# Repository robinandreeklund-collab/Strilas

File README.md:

# STRILAS

**Ballistic Laser Tactical-Engagement Simulator** — an open, DIY force-on-force training/gaming system. Players carry replica weapons that fire **coded infrared light** (not projectiles). Hits are registered by body/helmet detectors, ballistics and time-of-flight are simulated centrally, and every shot, movement, reload and hit is logged for live tracking and after-action review.

Think MILES / laser-tag, but with simulated ballistics, physical recoil feedback, NFC-based ammunition logistics, and an open telemetry stack you own.

> 📖 **Komplett systemguide (master-referens):** [`STRILAS-SYSTEM-GUIDE.md`](STRILAS-SYSTEM-GUIDE.md)
> — allt på ett ställe: arkitektur, ballistik/räckvidd, precision, hitbox, algoritm, optik, RTK-position,
> haptik, korten, batteritid, eye-safety, tillverkning, verifiering och repo-karta.
> Tillverkningsberedskap: [`vapen-stack/nextpcb/FORSTA-BATCH.md`](vapen-stack/nextpcb/FORSTA-BATCH.md).

---

## ⚠️ Safety first — read this before building anything

STRILAS is a **simulation and immersion** system. It does **not** fire projectiles and provides **no** uplift toward any real weapon. It does, however, contain three genuine hazards that you are responsible for handling correctly:

1. **Eye safety (IR laser).** The engagement emitter uses near-IR (~905 nm) which is **invisible**. Keep the optical output within **Class 1 (eye-safe)** limits and enforce the current limit **in hardware**, not just firmware. The risk is highest near the muzzle where players point at each other. If you are not confident you can keep it Class 1, use a diverged IR-LED emitter instead of a collimated laser diode.
2. **LiPo charging.** The base dock charges many lithium packs at once. This is the single largest fire risk in the project — larger than the laser. Use per-cell balancing, a real BMS, thermal monitoring, and a fire-safe charging area.
3. **High-current contacts.** The recoil rail carries ~20 A peaks through the magazine interface. Use contacts rated **> 25 A** and only ever make/break them **cold** (rail disabled during insert/extract — see the make-ready state machine).

**Replica / airsoft chassis:** STRILAS is typically built onto an airsoft replica body. Airsoft replicas are age- and region-restricted; check and follow your local laws for ownership, transport (e.g. muzzle covers / cases), and where you may use them. Treat and store the device responsibly and never carry it in public in a way that could be mistaken for a real firearm.

**Play safety:** eye protection (rated goggles) for all participants, defined play boundaries, and a clear "weapons safe" procedure.

---

## What it does

- **Coded IR engagement** — every shot transmits a packet (shooter ID, weapon profile, ammo/damage code). Detectors on harness + 360° helmet register hits and hit zones.
- **Simulated ballistics** — per-weapon/ammo profiles define muzzle velocity, drag model, drop and time-of-flight. Because the laser arrives instantly, the **server** adjudicates whether the simulated round would land, using both players' positions, the weapon's attitude and the computed flight time.
- **Physical recoil** — an electronic reciprocating-mass unit gives a real kick, scaled per weapon profile. The IMU senses the muzzle climb it causes and feeds it into the **next** shot's trajectory (the recoil-to-aim loop), so uncontrolled bursts walk off target.
- **NFC ammunition logistics** — each magazine carries a passive NFC tag (ID, capacity, rounds remaining). Inserting a mag sets the ammo counter; running dry blocks fire; reloading rewrites the tag to full at base.
- **Make-ready drill** — the recoil power rail (sourced from a battery inside the magazine) is enabled only after racking a charging handle, mirroring "chamber a round," and disabled before the magazine is released. This also guarantees the high-current contacts are always made/broken cold.
- **Live positioning & telemetry** — UWB (+ GNSS outdoors) gives sub-30 cm position; body/weapon IMUs give pose. Everything is timestamped to a shared clock.
- **After-action review** — weapon-cam video synced with the full event timeline, plus a live dashboard and map.

---

## How it works (engagement model)

```
trigger ──► IR emitter sends coded pulse ──► target detector registers strike
   │                                                  │
   └─► recoil unit fires (PWM scaled)                 │
   └─► IMU captures barrel attitude                   ▼
                                       SERVER adjudicates:
                                       shooter pos + target pos (UWB/GNSS)
                                       + barrel attitude (IMU)
                                       + simulated time-of-flight & drop
                                       ──► hit / miss / hit-zone outcome
```

The key design choice is **central, positional adjudication**: rather than computing the result on each weapon, the server knows where both parties are and how they are moving, and resolves the engagement with the simulated projectile's flight time. This is fairer for moving targets and is the basis for the analytics layer.

---

## Project map (design → validated → runnable)

This repo has grown from the spec above into a **physically-validated design with a runnable
reference implementation**. Where to look:

| Area | What | Where |
|---|---|---|
| **Analysis & BOM** | README review + state-of-the-art level-3 BOM + chosen dev boards | [`docs/hardware-analysis.md`](docs/hardware-analysis.md) |
| **Architecture** | geometric ballistic adjudication + fused pose stack (incl. precision ≠ beam width) | [`docs/level3-ballistic-architecture.md`](docs/level3-ballistic-architecture.md) |
| **System flow** | how it all connects (component map, shot sequence, pose layers) | [`docs/system-flowchart.md`](docs/system-flowchart.md) |
| **v1 build** | exact shopping list for a precise 100–150 m shooting test | [`docs/mvp-shooting-test-bom.md`](docs/mvp-shooting-test-bom.md) |
| **Weapon PCB** | optic module: camera + 2× 940 nm emitters + IMU + buck-CC driver (42×62 mm) | [`hardware/README.md`](hardware/README.md) |
| **Receiver PCBs** | vest detector patch + helmet halo (TSOP + 860 nm constellation + GNSS) | [`hardware/receiver-boards.md`](hardware/receiver-boards.md) |
| **Design resolution** | every open problem → decision (wavelength split, eye safety, etc.) | [`hardware/weapon-module-design-resolution.md`](hardware/weapon-module-design-resolution.md) |
| **Eye safety** | Class 1 current budget (script + report) | [`hardware/eye-safety-budget.md`](hardware/eye-safety-budget.md) |
| **Physics verification** | end-to-end @150 m (radiometry + Monte Carlo + link budget) | [`hardware/system-verification-report.md`](hardware/system-verification-report.md) |
| **Firmware/CV** | runnable, hardware-abstracted chain (CV → fire-control → server) — no HW needed | [`firmware/README.md`](firmware/README.md) |
| **3D simulator** | interactive level-3 pipeline in the browser | [`sim/README.md`](sim/README.md) |

Run it (no hardware): `python3 -m firmware.run_demo` · `python3 -m firmware.test_chain` ·
`python3 hardware/system_physics_verification.py`

The key design choice — **central, positional adjudication** — is fully realized in
[`firmware/adjudicator.py`](firmware/adjudicator.py): the server knows where both parties are and
how they move, and resolves the engagement with the simulated projectile's flight time.

---

## System architecture

```
PLAYER NODE ×N
  ├─ Weapon unit (ESP32 + IMU)   ── ballistics, recoil control, state machine, radio
  ├─ IR emitter (905 nm, coded)
  ├─ Recoil unit (reciprocating mass)   ◄── powered by magazine LiPo via load-switch
  ├─ Harness + 360° helmet detectors
  ├─ Magazine (NFC tag + recoil LiPo + power contacts)
  ├─ Charging-handle & mag-release sensors  (make-ready / cold-mate sequencing)
  ├─ Internal logic cell  ── keeps node alive without a magazine
  └─ Weapon camera
        │  ESP-NOW / WiFi
        ▼
NETWORK (field)
  ├─ UWB anchors ×4–8   (sub-30 cm trilateration)
  ├─ WiFi mesh AP        (telemetry + video backhaul)
  └─ [optional] LoRa gateway + GNSS beacons   (large outdoor fields, coarse/long-range)
        │
        ▼
SERVER / EXERCISE CONTROL
  ├─ Hit adjudicator      (position + attitude + flight time → outcome)
  ├─ Position engine      (UWB + GNSS + IMU fusion → live map)
  ├─ Telemetry DB         (shots · movement · recoil · hits · ammo · make-ready)
  └─ AAR / replay + live dashboard
```

---

## Hardware (reference BOM, per player)

| Subsystem | Part (reference) | Notes |
|---|---|---|
| Weapon MCU | ESP32 (WiFi/BLE/ESP-NOW) | the brain; timing-critical IO |
| IMU | BNO085 (or BNO055) | barrel attitude + muzzle climb |
| IR emitter | 905 nm pulsed module + constant-current driver | **Class 1**, hardware current limit |
| Detectors | IR receiver array (harness) + 360° helmet sensor | hit + hit-zone |
| NFC reader | PN532 (I²C/SPI) + magwell switch | wakes on mag insert |
| Magazine tag | NTAG215 (passive) | ID / capacity / remaining |
| Recoil unit | reciprocating-mass actuator | ~0.12 kg moving mass, ~30 mm stroke |
| Recoil switching | logic-level MOSFET load-switch (>30 A) + flyback diode + 2×2200 µF low-ESR | soft-start |
| Magazine battery | high-discharge LiPo (≥25C) | powers recoil rail only |
| Logic battery | small internal 1S/2S cell + buck | keeps node alive without mag |
| Tracking | UWB tag (e.g. DW3000) + GNSS + body IMU | sub-30 cm + pose |
| Camera | ESP32-CAM / RunCam (5.8 GHz FPV or WiFi) | AAR + live |
| HUD | micro-OLED (SPI) | ammo · hits · weapon state |
| Sensors | charging-handle + mag-release micro-switches/hall | make-ready sequencing |

**Infrastructure:** UWB anchors ×4–8, WiFi mesh AP, server host, multi-bay LiPo charging dock (with BMS), optional Heltec CubeCell (HTCC-AB02S) boards as GNSS beacons / LoRa gateway for large outdoor fields.

> The CubeCell boards are **not** suitable as the weapon MCU (no WiFi/BLE, low-power M0+ core, LoRa is low-rate/duty-cycle-limited). Use them only for coarse outdoor GNSS beaconing or as a long-range LoRa gateway.

---

## Power architecture

Two physical sources, deliberately separated:

- **Logic rail** — internal cell → buck (3V3/5V) → MCU, IMU, IR driver, NFC, camera, OLED, radio. ~0.95 A average.
- **Recoil rail** — magazine LiPo → cold-mate power contacts → MOSFET load-switch (soft-start) → cap bank → recoil motor. ~4 A average, ~20 A peaks during full-auto.

The recoil rail is enabled by the MCU **only between "rack" and "mag release"**, so the magazine contacts are never made or broken under load.

---

## Make-ready state machine

```
NO MAG ──insert mag──► MAG IN (rail OFF, cold contacts)
                          │
                          └─ rack charging handle ─► validate (mag present, ammo>0)
                                                     ─► soft-start recoil rail
                                                     ─► chamber ─► READY (rail ON)
READY ──trigger──► IR + recoil, ammo−1 ──► READY
READY ──ammo == 0──► EMPTY (fire blocked, bolt-lock)
EMPTY ──swap mag + re-rack──► READY
ANY  ──mag-release──► drop rail FIRST ─► mag out (cold) ─► NO MAG
```

---

## Magazine NFC tag layout

| Field | Size | Contents |
|---|---|---|
| UID | 7 B | fixed magazine ID (read-only) |
| Capacity | 2 B | max rounds |
| Remaining | 2 B | current rounds |
| Profile | 1 B | weapon/ammo type |
| HMAC (optional) | 4–8 B | signature to prevent tampering |

Notes:
- The live count is held in **weapon RAM** while seated; the tag is written **once on extraction** (and once on base reload), staying well within EEPROM endurance.
- **Ammo count and battery charge are separate quantities.** Base reload is two decoupled cycles: a fast NFC ammo rewrite, and a slow BMS-managed battery charge. Keep a pool of magazines in rotation.
- For competitive integrity, sign `remaining` with an HMAC shared by weapon and base; mirror counts server-side per mag ID as backup.

---

## Weapon profile (example)

```yaml
# profiles/m4_556.yaml
name: "M4 / 5.56 sim"
muzzle_velocity_mps: 880
drag_model: G7
ballistic_coefficient: 0.151
rof_rpm: 720           # capped by recoil cycle time (~12 Hz)
recoil_pwm: 0.65       # 0..1 felt-recoil scale
mag_capacity: 30
damage_code: 0x12
```

---

## Repository structure

```
strilas/
├─ firmware/
│  ├─ weapon-node/        # ESP32: ballistics, recoil FSM, IR, NFC, IMU, radio
│  ├─ tracking-tag/       # UWB + GNSS + IMU beacon
│  ├─ base-dock/          # NFC rewrite + charge sequencing + logging
│  └─ detectors/          # harness / helmet receiver
├─ server/
│  ├─ adjudicator/        # positional hit resolution + flight-time model
│  ├─ position-engine/    # UWB/GNSS/IMU fusion
│  ├─ telemetry-db/       # time-series store
│  └─ dashboard/          # live map + AAR replay
├─ hardware/
│  ├─ weapon-unit/        # schematics, PCB, enclosures
│  ├─ magazine/           # tag + LiPo + contacts
│  └─ base-dock/          # multi-bay charger + BMS
├─ profiles/              # weapon/ammo YAML
├─ docs/
│  └─ strilas-systemritning.html   # full schematic set
└─ README.md
```

---

## Build & flash (outline)

> Detailed per-module instructions live in each subfolder's README.

```bash
# Weapon node (ESP32, PlatformIO)
cd firmware/weapon-node
pio run -t upload

# Server (dev)
cd server
docker compose up        # adjudicator + position-engine + telemetry-db + dashboard
```

Configuration (network keys, UWB anchor coordinates, weapon profiles) is set in `config/` — see `config/example.env`.

---

## Calibration & pre-game checklist

- [ ] IR emitter verified within Class 1 limits (hardware current limit confirmed).
- [ ] IR/detector boresight and range check; hit-cone divergence set per play style.
- [ ] UWB anchors surveyed; position fix < 30 cm in the play area.
- [ ] Recoil rail soft-start verified; no contact arcing on rack/mag-release.
- [ ] Magazine tags initialised (ID, capacity, profile); base reload writes full.
- [ ] All LiPos balanced/charged on the BMS dock; no swollen cells.
- [ ] Clocks synced across nodes (NTP/PTP); telemetry logging confirmed.
- [ ] Eye protection issued; boundaries and "weapons safe" briefed.

---

## Roadmap

- [ ] Environmental ballistics (wind, temperature) in the flight model.
- [ ] AR reticle/HUD overlay in the optic.
- [ ] Auto-generated engagement clips in AAR (tag video by event).
- [ ] Optional LoRa layer for large outdoor fields.
- [ ] Bolt-lock-back + muzzle-report audio for empty/feedback realism.

---

## Contributing

Issues and PRs welcome. Please keep the safety constraints (IR class, cold-mate contacts, BMS charging) non-negotiable in any hardware change, and document power/timing implications for changes that touch the recoil or engagement path.

---

## License

- Code: MIT
- Hardware: CERN-OHL-S
- Docs: CC BY 4.0

*(Adjust to taste before publishing.)*

---

*STRILAS is a training/gaming simulator. It is not a weapon and provides no real-world weapon capability. Build and operate it responsibly and within your local laws.*

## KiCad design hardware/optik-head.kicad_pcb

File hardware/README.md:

# STRILAS — Hårdvaruritningar

Två fysiskt skilda noder, två kort:

| Kort | Nod | Funktion | Doc |
|---|---|---|---|
| **Vapnets optikmodul** | vapen | precis sikteskamera + IR-**sändare** (940 nm) + IMU + driver | nedan |
| **Väst-detektor-patch** | väst | IR-**mottagare** (TSOP 940 nm) + 860 nm-konstellation | [receiver-boards.md](receiver-boards.md) |
| **Hjälm-halo** | hjälm | 8× TSOP 360° + 860 nm-konstellation + **GNSS-patch** | [receiver-boards.md](receiver-boards.md) |

*(Föråldrad: `detector-ring-8x-tsop4856` hade kamera i mitten — player har ingen kamera; ersatt av väst-patch + hjälm-halo.)*

---

## 1. Vapnets optikmodul v1 (KOMPAKT) — sikteskamera + 2× IR-emitter + IMU + driver

**Allt vapnet behöver** på ett kort: precist sikte, skottstråle, attityd och driver.
Krympt från Ø80 (4 emittrar) till **42×62 mm** *utan prestandaförlust*. Genereras av
[`weapon_emitter_layout.py`](weapon_emitter_layout.py).

> **Full designupplösning (alla problem → beslut):** se
> [`weapon-module-design-resolution.md`](weapon-module-design-resolution.md).

**Precisionen** kommer från **sikteskameran** (centrum) som mäter bäringen till målets
IR-konstellation → sub-0,1° (se `../docs/level3-ballistic-architecture.md` §3.2) — den är
**oförändrad oavsett emitterantal**. **Skottet** är de 2 kollimerade emittrarna, symmetriskt
ovanför kameran → **samboresikt** (parallax ~0,01° @150 m; bred kon = bara LOS/ID).

### Vad som sitter på kortet

| Ref | Del | Roll |
|---|---|---|
| (mitten) | **Sikteskamera: OV5647 NoIR + 860 nm bandpass + M12 (FOV 15–30°)** | **PRECISION** — ser konstellationen → solvePnP → bäring (rolling shutter; fast-pan-grind i firmware) |
| D1–D2 | **940 nm OSLON Black** ×2 + **Carclo 10195** (~Ø20) kollimator | **skott** — kodad 56 kHz-stråle, 100–150 m |
| U2 | **TDK ICM-45686 IMU (SPI)** | attityd mellan kamerabildrutor + rekyl; **array borttagen — verifierat 1 räcker** (drift 0,0005°) |
| U6 / L1 / Rsense | **buck konstantströms-LED-driver** (från 2S) / induktor / sense-resistor | konstantström + **hårt HW-tak = ögonsäkerhet** |
| C1 / Cin / D5 / Q1 | Cout 220 µF / in-cap / freewheel-diod / AO3400 **56 kHz-gate** | switch-passiva + bärvågs-gate |
| Q2 / TVS / F1 | reverse-FET / clamp / PTC | inskydd på VBAT |
| J1 | **2×5 SPI:** VBAT·EN·IR_MOD·SCK·MOSI / GND·3V3·GND·MISO·CS | mot ESP32-P4 (kamera via FFC) |

### Mått & el — och varför prestandan hålls

- Kort **42 × 62 mm** (rundad rektangel), 3× M2.5. **~48 % mindre yta än Ø80**, halva bredden.
- **2 LED i serie** delar effektlasten → 100–150 m bibehålls; **VBAT 2S in**, U6 **buck-CC** steg ner (boost ej nödvändig); **IR_MOD** = 56 kHz på Q1-gaten.
- **1 IMU på SPI** (SPI för hög ODR vid rekyl). Array **borttagen** — fysik-verifieringen visade inter-frame-drift 0,0005° ≪ krav.
- **Precision = kameran** (emitter- & IMU-antal påverkar inte rubrik-precisionen — kameran 90 fps GS är primär referens).

### ✅ Självbländning — LÖST via våglängdssplit

**SKOTT = 940 nm**, **kamera = 860 nm bandpass** → kameran **avvisar sina egna emittrar**.
Inget timing-/baffelberoende (baffel kvar som backup). Bonus: 940 nm = TSOP-topp, 860 nm =
bättre kisel-QE för konstellationen. (Detaljer: design-resolution §0.)

### ⚠️ Ögonsäkerhet (mätpunkt)

Buck-CC-drivern (U6) ger **hårt HW-strömtak** (sense-resistor; firmware bara lägre).
**150 m kräver ~2 A** med medium-lins (10195) → Eavg ≈ 18× *punktkälle*-MPE @100 mm; **extended-
source-relaxationen täcker** men **måste mätas** (AE/skenbar källa per IEC 60825-1).
**Bringup: börja 1 A.** Notera: **ögonexponeringen sätts av 150 m-räckviddskravet (~Ie 59 W/sr),
ej av linsvalet** — medium @ 2 A ≈ minsta möjliga exponering. (Verifiering + design-resolution §3.)

### ⚠️ Kamera = OV5647 (kit), men MÅSTE vara NoIR

Kit-kameran är **Raspberry Pi Camera Model B = OV5647** (5 MP, 1/4″, M12 6 mm/F2.0/60,6° diag),
P4-stödd. **MEN spec säger "IR night vision: nonsupport" → den har IR-cut-filter och ser INTE
860 nm.** Vår precisionsväg kräver att kameran ser målets 860 nm-konstellation, så:
**du måste använda NoIR-varianten** (ta bort IR-cut-filtret, eller köp RPi NoIR-kameran).
Utan det ser sikteskameran ingen konstellation.

- **Stock-lins 6 mm/F2 (~33° H):** fungerar (verifierat SNR ≈ 30 @150 m, kort exp) men mindre
  marginal. **M12-linsen är utbytbar** → längre brännvidd ger mer räckvidd/SNR om du vill.
- Rolling shutter hanteras med kort exponering + modulerade LED + **fast-pan-grind** i firmware.

**GS-uppgradering om grinden blir för begränsande:** **ams-OSRAM MIRA220MINI MONO** (global shutter,
NIR) — köpbar (DigiKey **~$141**), men **eval-/sensorkort**, inte ett färdigt kit → P4-integration
gör du själv (ams-OSRAM-exempel finns); footprint ur deras öppna PCB-filer.

**Inte** IMX296/Arducam Pivariety (= Pi). Fullt kameraval: [`camera-selection.md`](camera-selection.md).

---

## 2. Detektor-ring (MÅLSIDAN) — 8× TSOP4856 + kamera

**Målets/västens** mottagarmodul (du skjuter MOT den) — 8 IR-mottagare i ring runt en
kamera. Genereras av [`detector_ring_layout.py`](detector_ring_layout.py). Separat nod
från vapnet; specen för mått/avkoppling/360°-täckning står i skriptets noter.

> Den här hör hemma på målet/västen, inte på vapnet — vapnet **sänder** (kort 1),
> målet **tar emot** (kort 2).

---

## Nästa steg mot riktig PCB

Dessa ritningar → KiCad: SFH 4715AS- + TSOP4856- + kameramodul-footprints, dragning till
header. Säg till så genererar jag KiCad-footprintsen och ett schema.

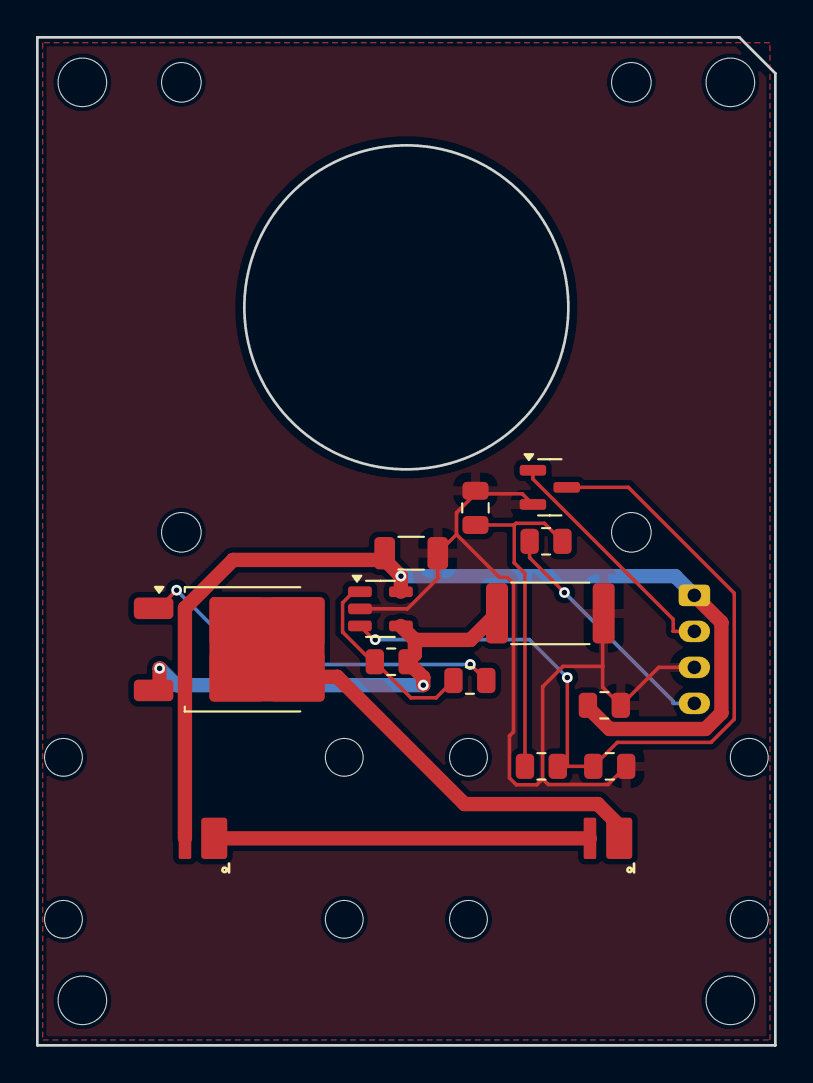
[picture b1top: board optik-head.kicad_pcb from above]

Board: 2 copper layers, 41.0 x 56.0 mm, 31 parts (1 on the bottom side), 11 nets.

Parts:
C1: 100nF; R_0805_2012Metric
C2: 100pF; R_0805_2012Metric
C3: 22uF; C_1206_3216Metric
C4: 1uF; C_0805_2012Metric
CAM1, CAM2, CAM3, CAM4: MountingHole_2.2mm_M2
CL1, CL2, CL3, CL4, CL5, CL6, CL7, CL8: MountingHole_2.1mm
D1, D2: SFH4725AS_940nm; IR_Emitter_OSRAM_OSLON_Black_SFH4725S
J1: →HAT (VBAT·IR_MOD·GND·EMIT_SET); JST_PH_B4B-PH-K_1x04_P2.00mm_Vertical
MH1, MH2, MH3, MH4: MountingHole_2.7mm_M2.5
Q1: AOD4184A; TO-252-2
Q3: AO3400; SOT-23
R1: 0R068; R_2512_6332Metric
R3: 15k; R_0805_2012Metric
R4: 1k; R_0805_2012Metric
R5: 100R; R_0805_2012Metric
R7: 10k; R_0805_2012Metric
U1: OPA171; SOT-23-5

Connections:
DRV_GATE: Q1.1, R5.2
EMIT_SET: J1.4, R7.1
GND: C1.2, C3.2, C4.2, J1.3, Q3.2, R1.2, R4.2, U1.2
IDRV_REF: Q3.3, R3.2, R4.1, U1.3
IDRV_SENSE: C2.2, Q1.3, R1.1, U1.4
IR_MOD: J1.2, Q3.1
LED_CATH: D2.2, Q1.2
LED_MID: D1.2, D2.1
OPA_OUT: C2.1, R5.1, U1.1
VBAT: C1.1, C3.1, D1.1, J1.1, U1.5
V_SET: C4.1, R3.1, R7.2

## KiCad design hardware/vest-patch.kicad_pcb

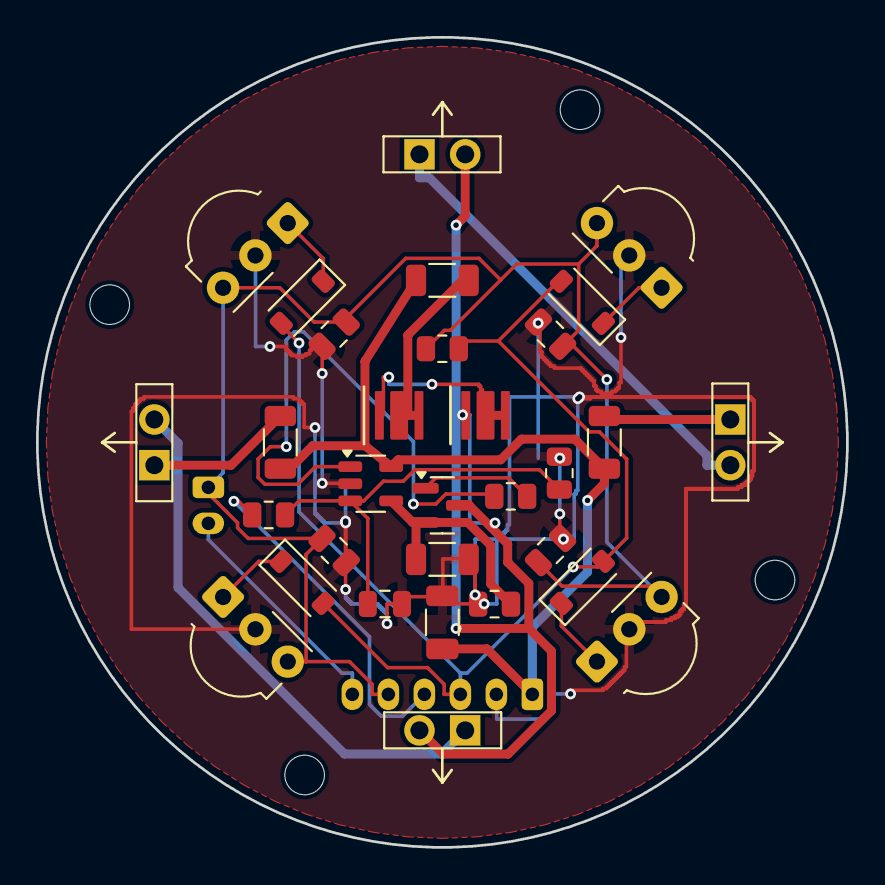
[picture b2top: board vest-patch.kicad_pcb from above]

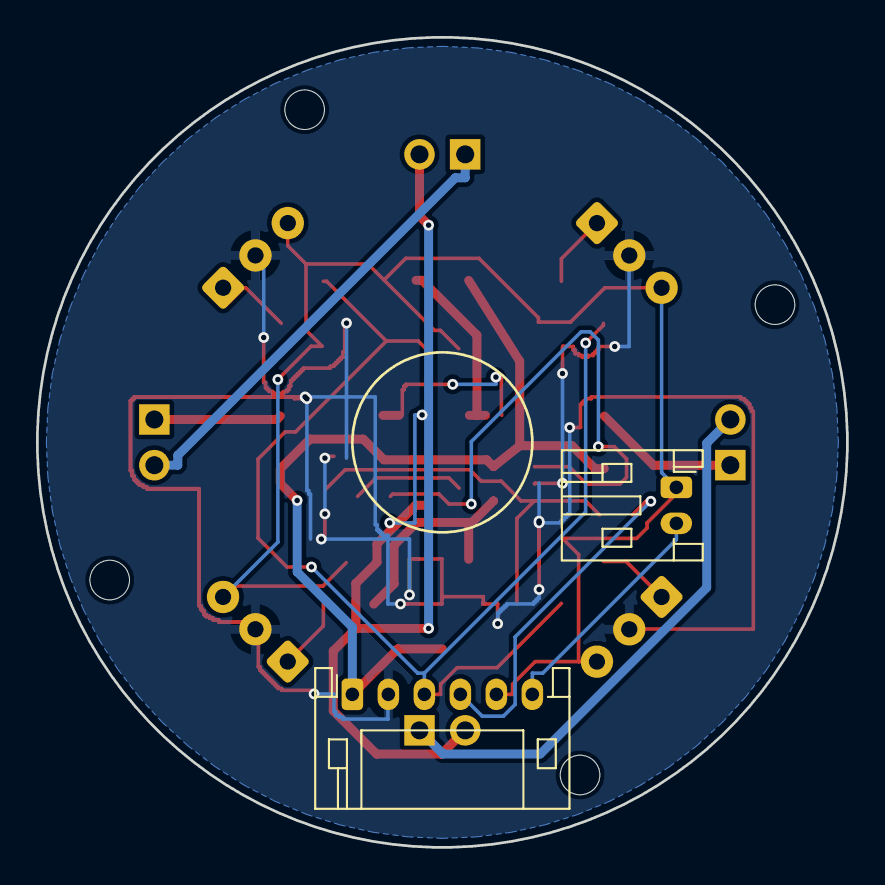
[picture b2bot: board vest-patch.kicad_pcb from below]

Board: 2 copper layers, 45.0 x 45.0 mm, 38 parts (3 on the bottom side), 21 nets.

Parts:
C1: C_1206_3216Metric
C2, C3, C4, C5: C_0805_2012Metric
C6: 22nF; C_0805_2012Metric
D1, D2, D3, D4: D_SOD-123
D5, D6: L1I0_IR
D7, D8, D9, D10: LED_Tab
H1, H2, H3, H4: MountingHole_2.2mm_M2
J1: JST_PH_S6B-PH-K_1x06_P2.00mm_Horizontal
J2: JST_PH_S2B-PH-K_1x02_P2.00mm_Horizontal
MK1: ERM_Coin_Keepout_10mm
Q1: SOT-23
R1, R2, R7, R8, R9: R_0805_2012Metric
R3, R4, R5, R6: R_1206_3216Metric
U1, U2, U3, U4: Vishay_MOLD-3Pin
U5: SOT-23-5

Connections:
+3V3: C2.1, C3.1, C4.1, C5.1, J1.5, J2.1, R1.1, U1.3, U2.3, U3.3, U4.3
DATA: D1.2, D2.2, D3.2, D4.2, J1.3, R1.2
GND: C1.2, C2.2, C3.2, C4.2, C5.2, C6.2, J1.2, R6.2, R7.1, R9.2, U1.2, U2.2, U3.2, U4.2, U5.2
IDRV_REF: C6.1, R8.2, R9.1, U5.3
IDRV_SENSE: Q1.2, R6.1, R7.2, U5.4
LED_A1: D5.1, R3.2
LED_A2: D7.1, R4.2
LED_A3: D9.1, R5.2
LED_CATH: D6.2, D8.2, D10.2, Q1.3
LED_EN: J1.4, R8.1
LED_GATE: Q1.1, R2.2
LED_M1: D5.2, D6.1
LED_M2: D7.2, D8.1
LED_M3: D9.2, D10.1
unnamed: R2.1, U5.1
OUT1: D1.1, U1.1
OUT2: D2.1, U2.1
OUT3: D3.1, U3.1
OUT4: D4.1, U4.1
VBAT: C1.1, J1.1, R3.1, R4.1, R5.1, U5.5
VIB: J1.6, J2.2

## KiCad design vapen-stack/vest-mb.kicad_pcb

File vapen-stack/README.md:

# STRILAS — vapen-stack (ren leveransmapp)

Allt för den kompletta vapen-stacken i **en mapp**: tre kort, hopsättnings-STEP,
verifiering och komplett BOM. Källkoden (generatorerna) ligger kvar i `../hardware/`.

## Stacken (uppifrån och ned)
```
FC-kort   (fire-control)  ── socket J1 → P4 edge A (12)  ·  J2 → P4 edge B (3V3-tapp)
ESP32-P4  (Waveshare)     ── edge A uppåt (FC) · edge B nedåt (optik)
Optik     (weapon-module) ── socket J1 → P4 edge B (14)  ·  lins Ø16 fram
```
Kraft: **batteri → optik J2 → VBAT → P4 VSYS → P4-regulator → 3V3 → alla kort**
(FC tar 3V3 direkt från edge B via J2 — ingen kabel/bygel).

## Filer

**Färdiga kort (beställ/tillverka):**
| Kort | PCB | 3D | Gerbers |
|---|---|---|---|
| Optik | `weapon-module.kicad_pcb` | `weapon-module.step` | `weapon-module-gerbers.zip` |
| P4-carrier* | `p4-board.kicad_pcb` | `p4-board.step` | — (köps, ej PCB) |
| Fire-control | `firecontrol.kicad_pcb` | `firecontrol.step` | `firecontrol-gerbers.zip` |

\* P4 = köpt **Waveshare ESP32-P4-WIFI6**. `p4-board.*` är mekanik-/headermodell.

**Hopsättning i Fusion (co-orienterade — droppa in vid origo, utan rotation):**
`weapon-module.step` (ankare) · `p4-board-stack.step` · `firecontrol-stack.step`
→ lyft P4 och FC i Z (~socket+header-höjd). USB-kabelpluggen i J_CAM kräver
clearance i P4↔optik-gapet.

**Färdig hop-assembly (allt i en fil):** `strilas-assembly.step` — alla tre korten
i en STEP, co-orienterade, **12 mm plan-till-plan** (optik z0 · P4 z12 · FC z24).
Standoffs läggs in av användaren. Regenereras med `python3 merge_assembly_step.py`
(kräver `pip install cadquery` — bygger en korrekt OCCT-assembly, stel Z-placering).

**BOM:** `BOM.csv` · `BOM.md` (komplett, alla kort + externa moduler). Regenereras
med `python3 gen_bom.py`.

**Verifiering:** `python3 system_sim.py` → ström-/signalflöde över kortgränserna
(0 typkrock · 0 utan ström · 0 dinglar). Bilder (regenereras ur live-netlista/-geometri):
- `port-matching.png` — varje stift etiketterat, mate-par med ✓ (`render_port_labels.py`)
- `edgeB-match-proof.png` — edge B↔optik: alla 14 stift + 4 hål, standoff-låst,
  speglad mate J1.k↔P4-stift(15-k), verifierad 0.000 mm (`render_edgeb_proof.py`)
- `system-flow.png` — kraft-/databuss-översikt

> **Mate (verifierat 0.000 mm mot _pads_z-geometrin):** P4 edge B är flippad till baksidan
> (J_B) → STACKAD/speglad mate, så optik **J1.k ↔ P4 edge B-stift (15-k)** (J1.1↔GPIO32 …
> J1.14↔VSYS). Edge A (FC) är på framsidan → RAK mate (FC J1.k ↔ edge A-stift k+5).
> De 5 IMU/SPI-näten ligger på J1-stift {1,2,4,6,7} = GPIO {32,27,26,23,22} och är
> permuterade för planär (korsningsfri, via-fri) routning IMU→J1 på F_Cu.

**Footprints:** `strilas.pretty/` (IR-emitter + ICM-456xx IMU).

**Design-noter:** `firecontrol.md` · `weapon-module-fab.md`

## Regenerera (källa i ../hardware/)
```
python3 hardware/weapon_module_netlist.py   &&  python3 hardware/receiver_place.py weapon
python3 hardware/make_p4_board.py
python3 hardware/firecontrol_netlist.py     &&  python3 hardware/receiver_place.py firecontrol
python3 hardware/export_stack_step.py        # co-orienterade STEP
```

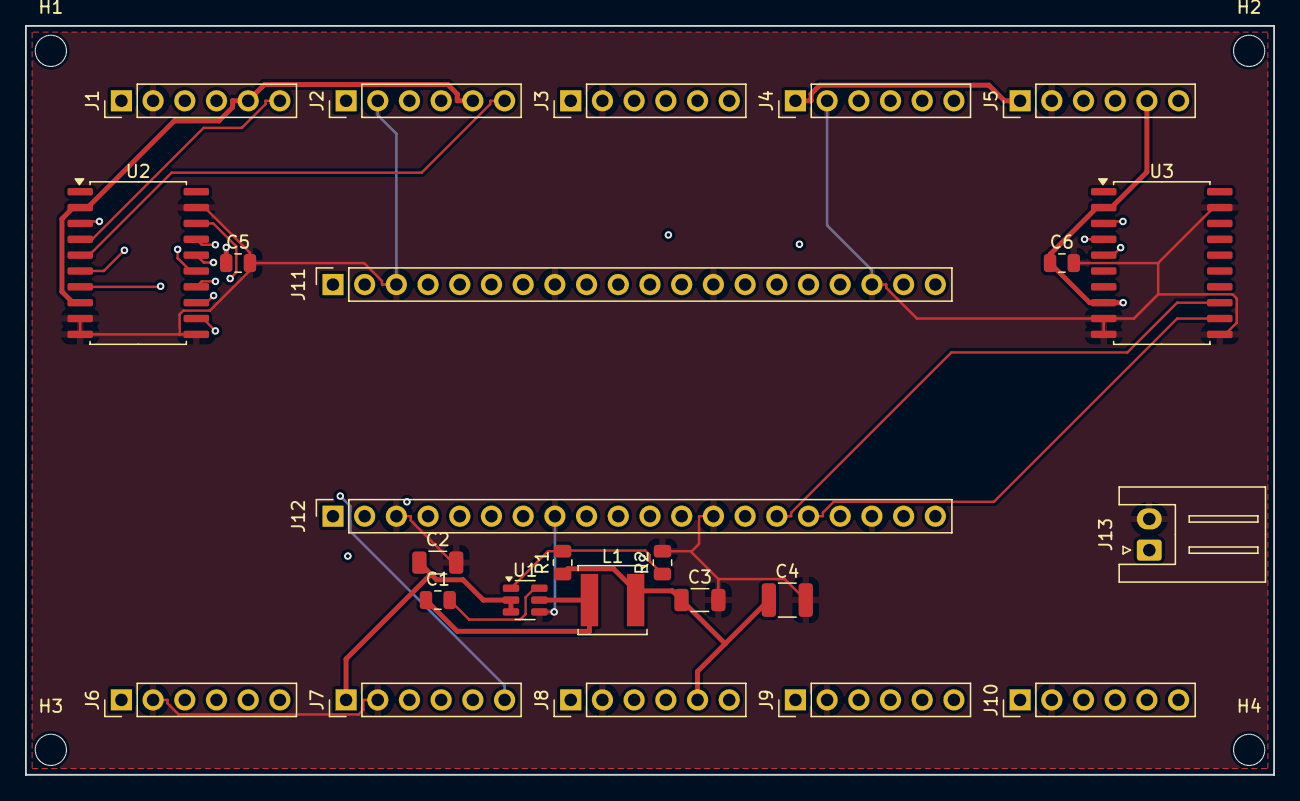
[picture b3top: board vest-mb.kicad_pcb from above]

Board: 4 copper layers, 100.0 x 60.0 mm, 29 parts (0 on the bottom side), 31 nets.

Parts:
C1, C5, C6: C_0805_2012Metric
C2, C3: C_1206_3216Metric
C4: C_1210_3225Metric
H1, H2, H3, H4: MountingHole_2.5mm
J1, J2, J3, J4, J5, J6, J7, J8, J9, J10: PinHeader_1x06_P2.54mm_Vertical
J11, J12: PinSocket_1x20_P2.54mm_Vertical
J13: JST_XH_S2B-XH-A_1x02_P2.50mm_Horizontal
L1: L_Changjiang_FNR5040S
R1, R2: R_0805_2012Metric
U1: TSOT-23-6
U2, U3: SOIC-20W_7.5x12.8mm_P1.27mm

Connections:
+3V3: C3.1, C4.1, C5.1, C6.1, J1.5, J2.5, J3.5, J4.5, J5.5, J6.5, J7.5, J8.5, J9.5, J10.5, L1.2, R1.1, U2.2, U2.8, U3.2, U3.8
BST: C1.2, U1.6
DATA1: J1.3, J12.1
DATA2: J2.3, J12.2
DATA3: J3.3, J12.4
DATA4: J4.3, J12.5
DATA5: J5.3, J12.6
DATA6: J6.3, J12.7
DATA7: J7.3, J12.9
DATA8: J8.3, J12.10
DATA9: J9.3, J12.11
DATA10: J10.3, J12.12
FB: R1.2, R2.1, U1.1
GND: C2.2, C3.2, C4.2, C5.2, C6.2, J1.2, J2.2, J3.2, J4.2, J5.2, J6.2, J7.2, J8.2, J9.2, J10.2, J11.3, J11.8, J11.13, J11.18, J12.3, J12.8, J12.13, J12.18, J13.2, R2.2, U1.4, U2.9, U2.10, U2.11, U2.19, U3.9, U3.10, U3.11, U3.19
LED_EN: J1.4, J2.4, J3.4, J4.4, J5.4, J6.4, J7.4, J8.4, J9.4, J10.4, J12.17
SW: C1.1, L1.1, U1.5
TPIC_CHAIN: U2.18, U3.3
TPIC_RCK: J12.16, U2.12, U3.12
TPIC_SER: J12.14, U2.3
TPIC_SRCK: J12.15, U2.13, U3.13
VBAT: C2.1, J1.1, J2.1, J3.1, J4.1, J5.1, J6.1, J7.1, J8.1, J9.1, J10.1, J11.2, J13.1, U1.2, U1.3
VIB1: J1.6, U2.4
VIB2: J2.6, U2.5
VIB3: J3.6, U2.6
VIB4: J4.6, U2.7
VIB5: J5.6, U2.14
VIB6: J6.6, U2.15
VIB7: J7.6, U2.16
VIB8: J8.6, U2.17
VIB9: J9.6, U3.4
VIB10: J10.6, U3.5

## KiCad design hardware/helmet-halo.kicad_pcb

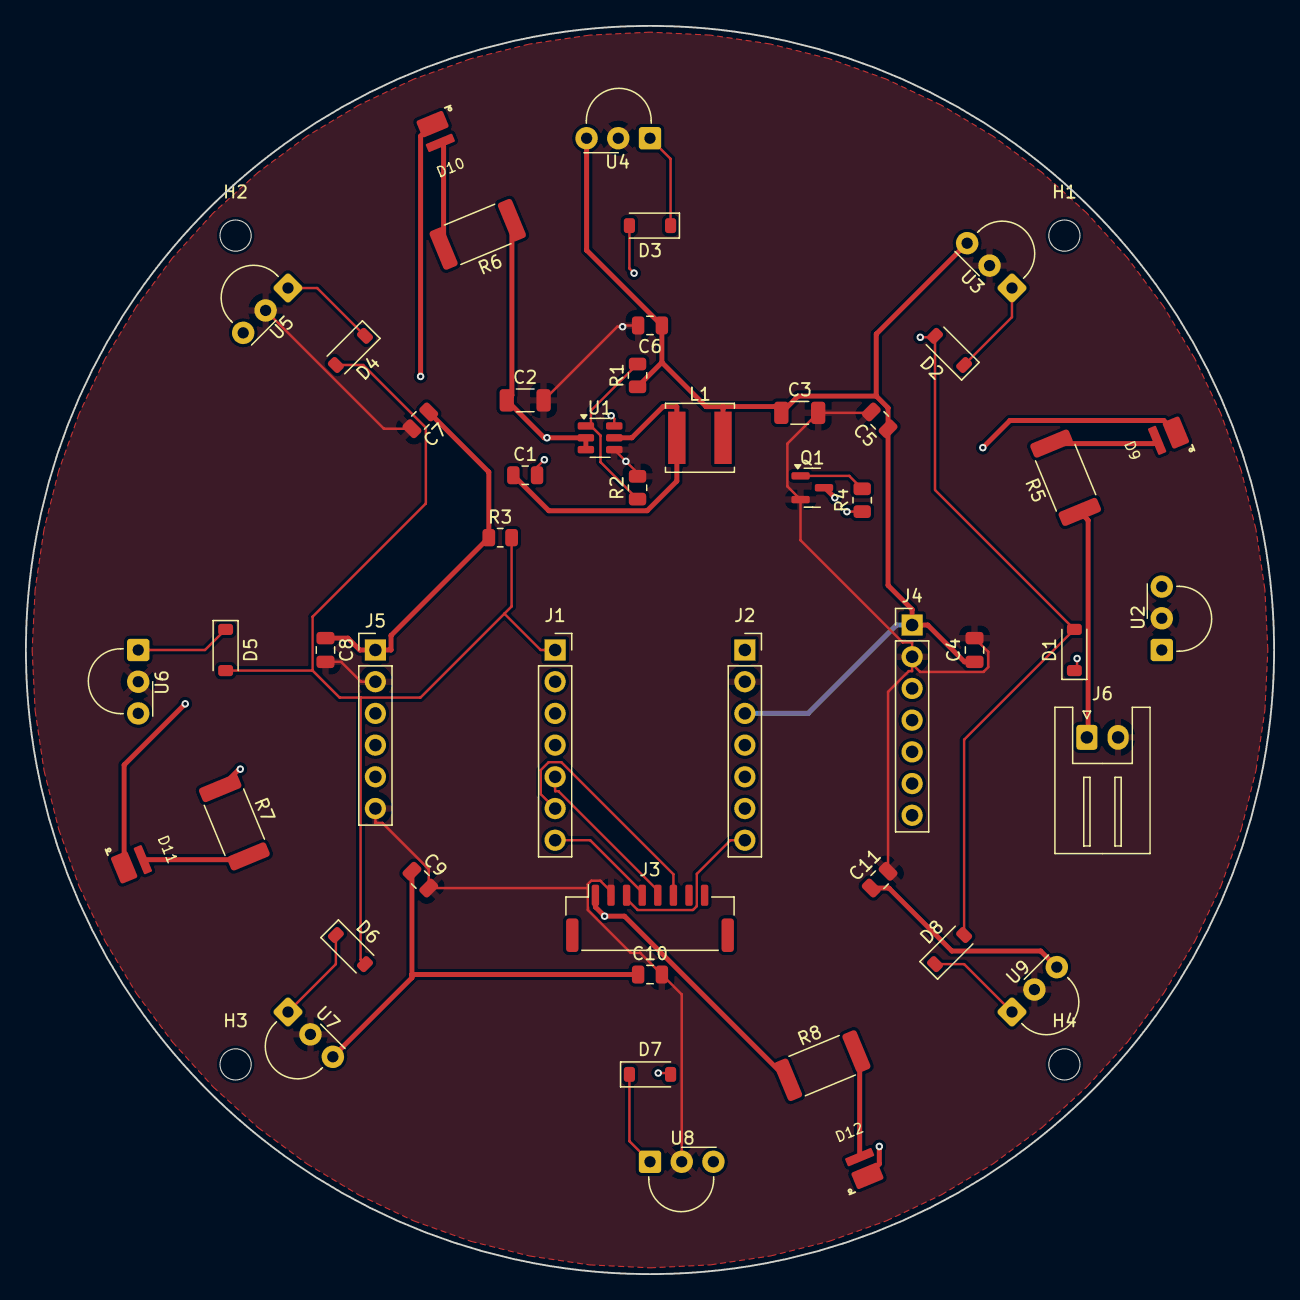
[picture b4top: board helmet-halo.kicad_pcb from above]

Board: 4 copper layers, 100.0 x 100.0 mm, 52 parts (0 on the bottom side), 31 nets.

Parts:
C1, C4, C5, C6, C7, C8, C9, C10, C11: C_0805_2012Metric
C2, C3: C_1206_3216Metric
D1, D2, D3, D4, D5, D6, D7, D8: D_SOD-123
D9, D10, D11, D12: IR_Emitter_OSRAM_OSLON_Black_SFH4725S
H1, H2, H3, H4: MountingHole_2.5mm
J1, J2: PinSocket_1x07_P2.54mm_Vertical
J3: JST_GH_SM08B-GHS-TB_1x08-1MP_P1.25mm_Horizontal
J4: PinHeader_1x07_P2.54mm_Vertical
J5: PinHeader_1x06_P2.54mm_Vertical
J6: JST_XH_S2B-XH-A_1x02_P2.50mm_Horizontal
L1: L_Changjiang_FNR5040S
Q1: SOT-23
R1, R2, R3, R4: R_0805_2012Metric
R5, R6, R7, R8: R_2512_6332Metric
U1: TSOT-23-6
U2, U3, U4, U5, U6, U7, U8, U9: Vishay_MINIMOLD-3Pin

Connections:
+3V3: C3.1, C4.1, C5.1, C6.1, C7.1, C8.1, C9.1, C10.1, C11.1, J2.3, J4.1, J5.1, L1.2, R1.1, R3.1, U2.3, U3.3, U4.3, U5.3, U6.3, U7.3, U8.3, U9.3
AMP_SD: J2.4, J4.3
BST: C1.2, U1.6
DATA: D1.2, D2.2, D3.2, D4.2, D5.2, D6.2, D7.2, D8.2, J1.1, R3.2
FB: R1.2, R2.1, U1.1
GND: C2.2, C3.2, C4.2, C5.2, C6.2, C7.2, C8.2, C9.2, C10.2, C11.2, J2.2, J3.2, J4.2, J5.2, J5.6, J6.2, Q1.2, R2.2, U1.4, U2.2, U3.2, U4.2, U5.2, U6.2, U7.2, U8.2, U9.2
GNSS_RX: J1.7, J3.4
GNSS_TX: J2.7, J3.3
I2C_SCL: J1.6, J3.6
I2C_SDA: J1.5, J3.5
I2S_BCLK: J1.3, J4.6, J5.5
I2S_DIN: J2.5, J5.3
I2S_DOUT: J2.6, J4.5
I2S_LRCK: J1.4, J4.7, J5.4
LED_A1: D9.1, R5.2
LED_A2: D10.1, R6.2
LED_A3: D11.1, R7.2
LED_A4: D12.1, R8.2
LED_CATH: D9.2, D10.2, D11.2, D12.2, Q1.3
LED_EN: J1.2, R4.1
unnamed: Q1.1, R4.2
OUT1: D1.1, U2.1
OUT2: D2.1, U3.1
OUT3: D3.1, U4.1
OUT4: D4.1, U5.1
OUT5: D5.1, U6.1
OUT6: D6.1, U7.1
OUT7: D7.1, U8.1
OUT8: D8.1, U9.1
SW: C1.1, L1.1, U1.5
VBAT: C2.1, J3.1, J6.1, R5.1, R6.1, R7.1, R8.1, U1.2, U1.3

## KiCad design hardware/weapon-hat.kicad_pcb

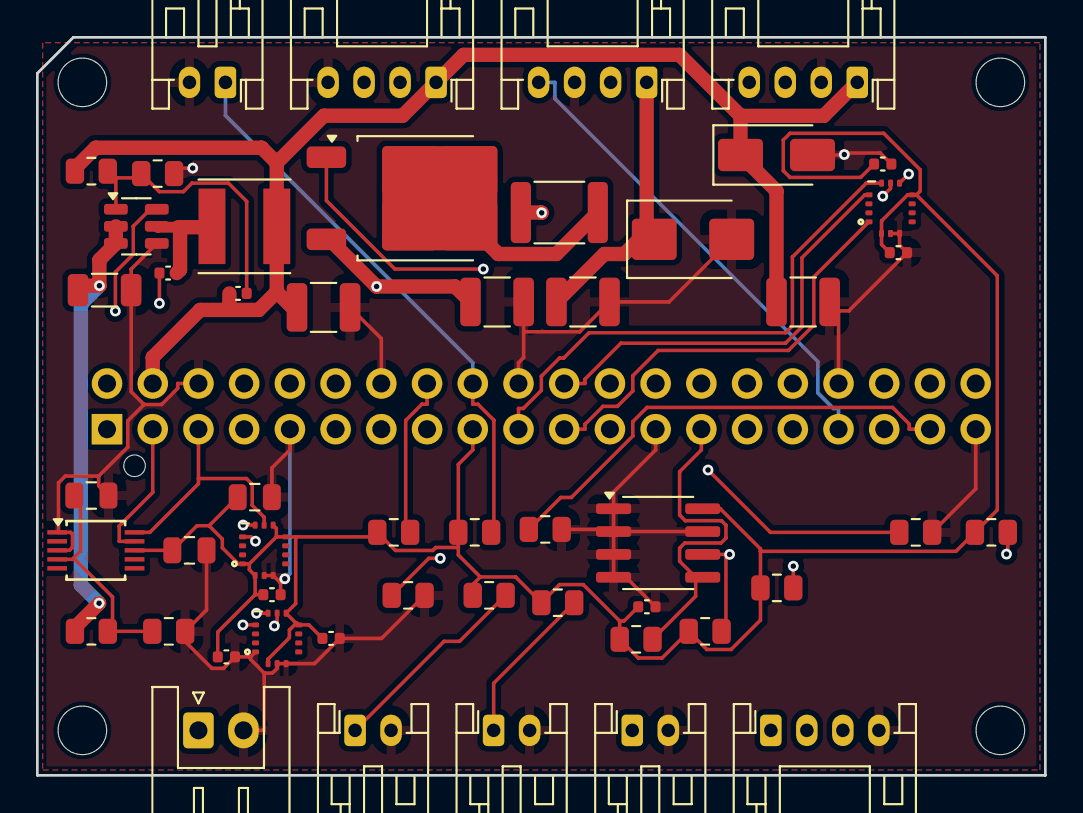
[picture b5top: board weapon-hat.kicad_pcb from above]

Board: 4 copper layers, 56.0 x 41.0 mm, 57 parts (1 on the bottom side), 34 nets.

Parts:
C1: 10uF; C_1206_3216Metric
C2, C15: 100uF; C_1210_3225Metric
C3, C4: 22uF; C_1210_3225Metric
C5: 22pF; C_0402_1005Metric
C6, C7, C9, C10, C11, C12, C16: 100nF; C_0402_1005Metric
C8: 1uF; C_0805_2012Metric
C13, C14: 100nF; C_0805_2012Metric
D1: SMBJ12A; D_SMB
D2: SMAJ5.0A; D_SMA
F1: PTC_3A; Fuse_1812_4532Metric
J1: 40-pin HONA → CM5-carrier (baksida, centrum); PinSocket_2x20_P2.54mm_Vertical
J2: 2S batteri (JST-XH); JST_XH_S2B-XH-A_1x02_P2.50mm_Horizontal
J3: → optik (VBAT·IR_MOD·GND·EMIT_HI; CC-sänka på opt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; JST_PH_S4B-PH-K_1x04_P2.00mm_Horizontal
J4: TRIGGER; JST_PH_S2B-PH-K_1x02_P2.00mm_Horizontal
J5: RACK; JST_PH_S2B-PH-K_1x02_P2.00mm_Horizontal
J6: MAGREL; JST_PH_S2B-PH-K_1x02_P2.00mm_Horizontal
J7: MAGWELL; JST_PH_S2B-PH-K_1x02_P2.00mm_Horizontal
J8: recoil-driver; JST_PH_S4B-PH-K_1x04_P2.00mm_Horizontal
J9: NFC (I²C); JST_PH_S4B-PH-K_1x04_P2.00mm_Horizontal
J10: ESP-brygga (extern, 5V·TX·RX·GND); JST_PH_S4B-PH-K_1x04_P2.00mm_Horizontal
L1: 2.2uH; L_Taiyo-Yuden_MD-5050
MH1, MH2, MH3, MH4: MountingHole_2.7mm_M2.5
PIN1: 40-pin pin1
Q1: AOD4185; TO-252-2
R1, R4: 100k; R_0805_2012Metric
R2: 52k3; R_0805_2012Metric
R3, R6, R7, R8, R9, R10, R11: 10k; R_0805_2012Metric
R5: 47k; R_0805_2012Metric
R12, R13: 4k7; R_0805_2012Metric
R14, R15: 3k9; R_0805_2012Metric
U1: AP63203WU 2S→5V 3A; TSOT-23-6
U2, U3, U4: ICM-42688-P; InvenSense_LGA-14_2.5x3mm_ICM-456xx
U5: ADS1115 I²C-ADC 0x48 (batteri-sense); TSSOP-10_3x3mm_P0.5mm
U6: AT24C32 HAT-ID EEPROM 0x50; SOIC-8_3.9x4.9mm_P1.27mm

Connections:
+3V3: C7.1, C8.1, C9.1, C10.1, C11.1, C12.1, C14.1, C16.1, J1.1, J1.17, R8.1, R9.1, R10.1, R11.1, R12.1, R13.1, R14.1, R15.1, U2.5, U2.8, U3.1, U3.5, U3.8, U3.12, U4.5, U4.8, U4.12, U5.8, U6.8
+5V: C4.1, C5.1, C15.1, D2.1, J1.2, J1.4, J9.1, J10.1, L1.2, R2.1
BST_n: C6.1, U1.6
EMIT_HI: J1.33, J3.4
ESP_RX: J1.10, J10.3
ESP_TX: J1.8, J10.2
FB_n: C5.2, R2.2, R3.1, U1.1
GND: C1.2, C2.2, C3.2, C4.2, C7.2, C8.2, C9.2, C10.2, C11.2, C12.2, C13.2, C14.2, C15.2, C16.2, D1.2, D2.2, J1.6, J1.9, J1.14, J1.20, J1.25, J1.30, J1.34, J1.39, J2.2, J3.3, J4.2, J5.2, J6.2, J7.2, J8.4, J9.2, J10.4, R1.2, R3.2, R5.2, R6.2, R7.2, U1.4, U2.6, U2.7, U3.6, U3.7, U4.1, U4.6, U4.7, U5.1, U5.3, U6.1, U6.2, U6.3, U6.4, U6.7
I2C_SCL: J1.5, J9.4, R12.2, U3.13, U4.13, U5.10
I2C_SDA: J1.3, J9.3, R13.2, U3.14, U4.14, U5.9
ID_SC: J1.28, R15.2, U6.6
ID_SD: J1.27, R14.2, U6.5
IMU2_INT: J1.29, U3.4
IMU3_INT: J1.31, U4.4
IMU_INT: J1.22, U2.4
IR_MOD: J1.12, J3.2
MAGREL: J1.16, J6.1, R10.2
MAGWELL: J1.18, J7.1, R11.2
MISO: J1.21, U2.1
MODE0: J1.37, R6.1
MODE1: J1.38, R7.1
MOSI: J1.19, U2.14
unnamed: Q1.1, R1.1
RACK: J1.15, J5.1, R9.2
RECOIL_FAULT: J1.36, J8.3
RECOIL_PWM: J1.32, J8.2
SCK: J1.23, U2.13
SW_n: C6.2, L1.1, U1.5
TRIG: J1.13, J4.1, R8.2
VBAT: C1.1, C2.1, C3.1, D1.1, J3.1, J8.1, Q1.3, R4.1, U1.2, U1.3
VBAT_F: F1.2, Q1.2
VBAT_IN: F1.1, J2.1
VBAT_SENSE: C13.1, R4.2, R5.1, U5.4
nCS: J1.24, U2.12

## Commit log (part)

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2026-06-14 Revise README for project clarity and detail
    Updated README to provide detailed project overview, safety guidelines, system architecture, hardware specifications, and build instructions.
2026-06-14 Add interactive 3D hardware simulator (web frontend)
    Self-contained Three.js app simulating the full STRILAS weapon with the
    selected hardware so nothing needs to be bought before the design is
    locked. Models (sim/hardware.js, ported from the Python sims):
    - SFH 4715AS IR link budget (range vs pulse current, beam angle, #LEDs,
    860nm filter, environment/sun) with a live ground range-ring
    - TSOP4856 body zones (head/chest/abdomen/legs) that flash on hit
2026-06-14 Add MVP shooting-test BOM (P4-WIFI6 kit x2 + discretes)
    Minimal buildable parts list: 2x ESP32-P4-WIFI6-KIT-A (P4+C6 WiFi6 +
    camera + speaker, identical hardware for weapon and target), plus a small
    bag of discretes (SFH4715AS IR LED + MOSFET driver + trigger for the
    weapon; TSOP4856 56kHz receivers for the target). One toolchain, camera +
    speaker in scope. Carrier-frequency match and eye-safety notes included.
2026-06-14 v1: make camera-bearing precision the core, defer GNSS/UWB
    Per the precision discussion, v1 now builds the optical precision mechanism in
    from the start: the sight camera measures relative bearing to the target's
    active IR LED constellation via solvePnP (sub-0.1deg), with the IMU filling
    between frames. This - not beam width - is the precision, and it is self-
    contained in the relative weapon->target frame, so GNSS-heading and UWB are NOT
    needed in v1 (deferred to field-scale multi-player). Weapon gains a telephoto
2026-06-14 Add Class 1 eye-safety current-budget calc (script + doc)
    Parametric IEC 60825-1 estimate for the 940nm shot emitter. Computes radiometry
    exactly (Ie, corneal irradiance at 100mm, eye power) vs a conservative point-
    source thermal MPE (~30.6 W/m^2, C4=3.02). Key honest finding: under the
    worst-case point-source assumption the Class 1 ceiling is only ~0.1A full-auto /
    ~0.67A semi (range-killing); but a LED+lens is an extended source, and if the
    measured apparent source >= alpha_max the limit relaxes ~67x, making 1-3A Class 1
2026-06-14 Add runnable firmware/CV skeleton (testable without hardware)
    Hardware-abstracted logic for the whole chain + a sim harness, so everything
    runs in code before any soldering. Modules: config (shared HW values), protocol
    (FireEvent/IRHit/Verdict), cv_pose (numpy blob detection + bearing/range pose),
    ballistics (3-DOF drop/TOF), adjudicator (server: geometry x IR-gate -> verdict),
    weapon_node / target_node (ESP-IDF-portable logic), world_sim (fake camera/IR/
    trigger). Key abstraction: WeaponNode.process_detections() takes detector output
2026-06-15 Kit camera is OV5647 (RPi Cam Model B), not OV5640 - and needs NoIR
    User confirmed the exact kit camera: Raspberry Pi Camera Model B = OV5647 (5MP
    1/4in, M12 6mm/F2.0/60.6deg diag), 'IR night vision: nonsupport'. Two design
    impacts captured across docs/firmware/verification:
    - Sensor renamed OV5640 -> OV5647 everywhere (both are P4-supported; OV5647 has
    its own ISP). Firmware FOV updated 18 -> 33.4deg (stock 6mm lens, swappable M12).
    - CRITICAL: the stock camera has an IR-cut filter -> it does NOT see 860nm. The
2026-06-15 Lock USB OV9281 GS NoIR (6mm) + P4 header-mount carrier; re-spin weapon board
    User locked: camera = single USB OV9281 global-shutter mono, 6mm no-distortion
    lens, NoIR (must be the no-IR-filter variant; stock 650nm filter blocks 860nm).
    Camera mounts behind the optic board (lens through the Ø16 hole) and connects to
    the P4 via USB cable (not the board header). P4 mounts as a carrier (header-mount):
    J1 changed 2x5 cable -> 2x6 P4-interface header (VSYS/3V3/GND/IR_MOD/SPI), plus J2
    battery input feeding VSYS + the emitter rail. Added the P4 GPIO pin-map
2026-06-15 Add camera mount (H4-H7, B0332 28x28) + resolve P4 connection (J1 cable)
    - 4x M2 camera-mount holes matching Arducam B0332 (38x38, 28x28 pattern) around
    the lens axis; camera bolts behind board, lens through Ø16. Repositioned parts
    to clear the holes; C2 220uF electrolytic -> 100uF 1210 MLCC (lower ESR, fits).
    - Re-routed: 24 comps, 176 tracks + 25 vias, 0 unrouted, 0 clearance viol @0.2mm.
    - P4 (ESP32-P4-WIFI6 = 71x21mm Pico-style) cannot stack behind the rear camera;
    J1 (2x6) carries VSYS/3V3/GND/IR/SPI/INT to P4 GPIO via short cable.
2026-06-15 P4 header (J1) onto BACK side + remove camera standoffs
    - J1 (P4 edge connector) now on B.Cu (shooter side): route with J1 on front
    (freerouting can't DSN a back-side fp), then flip left-right post-route -> single
    -column THT pads stay in place -> 0 unrouted preserved. Fixes 'header on wrong side'.
    - Removed Würth standoff 3D from camera holes H4-H7 (now plain M2 holes; user fits own).
    - 33 comps, 159 tracks + 24 vias, 0 unrouted, 0 clearance viol @0.2mm. Gerbers+STEP+render.
    https://claude.ai/code/session_01EQ2JhMHoLWtYkqqRi7brXM
2026-06-15 Weapon board: route P4-left layout fully clean (0 unrouted, 0 clearance)
    Routed the P4-left placement end to end:
    - IMU + decoupling moved next to J1 (left-centre, under P4) so all 5 SPI
    escapes are short — this resolved the MISO routing bottleneck that
    Freerouting hit with the IMU at the bottom.
    - power/protection strip on the right edge; Rset+bulk kept by the emitters.
    - connectors J1/J2/J3 flipped to back; 4-layer copper pours
2026-06-15 Fixa batteri-JST: kabelöppning pekade in i kortet efter back-flip
    flip_j1_back speglar kontaktkroppen topp-botten, vilket vände J2:s
    kabelöppning från nederkanten till INÅT kortet (kabeln hade fått dras
    tvärs över PCB:n). Placerar nu J2 rot180 (öppning uppåt före flip →
    nedåt efter) vid y=-25.3 → öppningen pekar mot nederkanten med ~2 mm
    marginal, hela kroppen på kortet, inga paddar utanför kant.
    Re-routat rent (0 oroutade, 0 clearance @0.2mm).
2026-06-15 Co-orienterade stack-STEP (P4+FC roterade till optikens frame)
    De tre kortfilerna låg i olika orientering (P4 rader i X, optik i Y) → vid rå
    stapling möttes fel rader och antalen krockade. export_stack_step.py beräknar
    2-punkts stela transformer ur faktiska padd-positioner och skriver
    p4-board-stack.step + firecontrol-stack.step FÖR-ROTERade till optik-framen.
    Verifierat: edge B↔optik-J1 och edge A↔FC-socket landar på 0.000 mm; rätt rader
    möts (14↔14, 12↔12). Z bakas ej — lyft P4/FC i Z i Fusion.
2026-06-15 Fix assembly-STEP: korrekt OCCT-merge (komponenter scattrade förut)
    Textmerge translaterade alla CARTESIAN_POINT i Z, vilket kastade iväg de
    mapped-item-placerade 3D-modellerna. Bygger nu assemblyn med cadquery/OCCT:
    varje kort laddas och får en STEL Location (z 0/12/24) — geometri orörd.
    Verifierat återinläst: 41 solider, bbox 54×86×39 mm, ingen scattering.
2026-06-16 Centroid även som .xls (NextPCB-uppladdning kräver zip/rar/xls/xlsx)
    https://claude.ai/code/session_01EQ2JhMHoLWtYkqqRi7brXM
2026-06-16 Ärlig precisionsanalys @150m med verkliga delar (OV9281 16mm + ICM-42670-P)
    vapen-stack/ritningar/precision-analys.md + precision-felbudget.png:
    - Felbudget 1σ ur verkliga specar. ICM-42670-P gyro RNSD=0,007°/s/√Hz (DS-000451).
    - Steady-state (mål i bild): RSS ~6,6 mm 1σ @150m ≪ hållpunkt 140 mm
    → spelaren/hållovern avgör träff, ej sensorbrus (= önskad 'måste-sikta').
    - IMU mellan-frame-drift 2,4 mm @60fps (ärlig nedgradering från 45686, OK).
    - SVAGHET: recoil kastar mål ur 13,7° FOV → IMU-dödräkning × skalfel = 0,26-1,6 m
2026-06-16 Helhetssystem: väst+hjälm verifierade mot vapnet + skytt↔mål-loop + hitbox-sim
    vapen-stack/ritningar/: system-helhet.png, hitbox-simulering.png, system-simulering.md
    - Väst/hjälm verifierade mot vapnet: 940nm skott↔TSOP4856, 860nm konstellation↔kamera.
    Väst 3×TSOP+2×860nm, hjälm 8×TSOP+4×860nm+GNSS, båda→väst-nod (4-pol).
    - Skytt↔mål-loop: 860nm konstellation→kamera (geometri=TRÄFF), 940nm skott→TSOP
    (LOS+ID=GATE). Träff = kamera-lösning på siluett OCH TSOP-LOS → aldrig point-and-shoot.
    - Hitbox/avstånd: torso 107/36/18px @25/75/150m; hållpunkt 4/34/136mm; sensor ~mm ≪ zon
2026-06-16 Återställ optik-BOM till matchande MPN (14/15) — ångra R2-split + in-stock-byten
    Mina 'in-stock'-byten gjorde matchningen sämre (14/15 → 11/15): FRC-resistor, JK-PTC,
    16V-cap blev pending. Återställt till de MPN som NextPCB faktiskt matchar:
    - R2: ångrade onödiga 2× 6R8-splitten → enkel 3R3 2W CRCW25123R30FKEGHP (matchad).
    Netlist + placement (R4 borttagen), optik omdragen ren (0 oroutade/clearance).
    - F1 → MF-MSMF075/16X-2 (matchad). C2 → 100µF 25V GRM32ER61E107ME20L (enda pending).
    - D2/D3 SFH4725S → Procurement 'C' (i BOM, NextPCB monterar, du levererar delen).
2026-06-16 Väst-MB: färdigställ "bänk-kvar" — buck-verifiering, 165/TPIC-drivrutin, LED_EN-analys
    De fyra öppna punkterna gjorda i beräkning/kod (ej lämnade som bänk-gissning):
    - Buck 3,3 V: Vout = 0,8·(1+31,6/10) = 3,328 V exakt (FB-delare); 4,7µH+22µF = AP63203
    typapp, rippel <10 mV. Deterministiskt — bänk bekräftar bara.
    - 165-läsning + TPIC-PWM: körbar drivrutin firmware/vest_mb_hw.py (MicroPython, XIAO-S3).
    Ett delat SPI-svep läser 74HC165 (hits, aktiv-låg) samtidigt som det skriver TPIC6B595
    (vibb-mönster); mjukvaru-PWM 16 steg/zon via timer; bit↔zon-map härledd ur netlistan.
2026-06-16 Rework väst- + hjälm-moderkort till ESP32-P4-WIFI6 (samma kort överallt)
    Byter nod-ESP på båda moderkorten från ESP32-C6-devkit till ESP32-P4-WIFI6
    — exakt samma kort som vapnets optikmodul — för enklare underhåll och en
    enda source genom hela systemet.
    - helmet_mb_netlist.py: C6 1x16-sockel → P4 2× 1x20 kant-sockel (edge A/B,
    pinout verifierad mot Waveshares datablad). Carrier-buck behålls (3V3 för
    laster); P4 självförsörjer via VSYS=VBAT. F9P + IIM-42653 + 4 TSOP + 2 LED
2026-06-16 Hjälm-mb → RUND board (Ø104) + fixa stale optik/IMU-kommentar
    - Hjälm-mb omplacerad cirkulärt (bbox-center på ring): P4 central horisontell,
    4 TSOP radiellt utåt på ringen (NÖ/NV/SV/SÖ, 360° huvudtäckning), 2 LED N/S,
    8 kontakter + 4 monteringshål jämnt runt kransen, buck/IMU/driver i crescents.
    Rund Edge.Cuts Ø104; cirkulär kopparplan (In2=+3V3). Routad rent 0/0/0,
    0 courtyard-krockar, inget utanför cirkeln. F9P-puck monteras på centrum.
    - Verifierat alla 5 fab-kort: 0 oanslutna, 0 clearance@0.2mm, footprints matchar
2026-06-17 Fixa batterikontakternas riktning (väst-mb J13 + hjälm J10) — öppning ut över kant
    Användarfeedback (väst-mb-bild): JST-batterikontakten öppnade inåt kortet (kabeln
    tvingades korsa kortet). Gäller båda moderkorten.
    - Väst-mb J13: flyttad till HÖGER kant, öppning +x rakt ut över kanten (rot90).
    - Hjälm J10: roterad så öppningen pekar RADIELLT UT mot kortkanten (azimut 245°, rot335),
    istället för in mot centrum.
    - Väst-mb +3V3-routning sprack när J13 flyttades (10 zon-kontakters +3V3-fanout är
2026-06-17 added
    p4 docs
2026-06-17 firecontrol: matcha P4-hålbild + header exakt (Ø1.7 standoff, J1 −18.31)
    FC-brädan stämde inte mot P4 i stacken:
    - Standoff-hålen H1-H4 var Ø2.2mm (MountingHole_2.2mm_M2) medan P4/optik
    har Ø1.7mm → "hålbilden skiljer". Nu Ø1.7mm via nytt bibliotek-footprint
    strilas:MountingHole_1.7mm (identiskt med optikens HP1-HP4 + P4 MP1-MP4).
    - J1 (P4 edge-A-socket) låg på x=−18.30 medan P4 J_A pad1 = −18.31
    → "header missar lite gran". Flyttad till exakt −18.31 (0.00mm offset,
2026-06-17 verify: rigoröst stack-verifieringsskript inför custom-PCB
    hardware/verify_stack.py kollar (ur korten): kontakt-gänga, optik J1↔P4 edge B
    + FC J1↔P4 edge A läge per stift + nät→GPIO, standoff-hålslinjering, GPIO-krock,
    DRC. Hittade: optik HP1-4 ligger 9.89 mm fel mot P4:s monteringshål (övrigt OK).
    https://claude.ai/code/session_01EQ2JhMHoLWtYkqqRi7brXM
